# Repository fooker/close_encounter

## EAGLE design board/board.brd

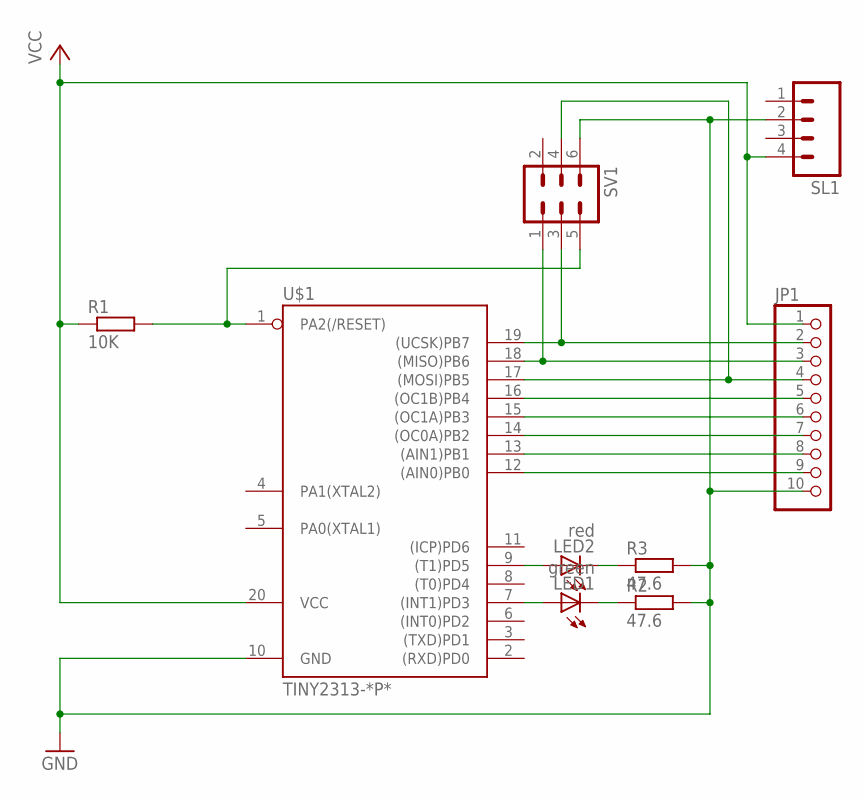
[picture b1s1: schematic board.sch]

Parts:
JP1: PINHD-1X10; 1X10
LED1: green; LED3MM
LED2: red; LED3MM
R1: 10K; 0207/2V
R2, R3: 47.6; 0207/2V
SL1: M04; 04P
SV1: ML6
U$1: TINY2313-*P*; DIL20

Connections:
GND: JP1.10, R2.2, R3.2, SL1.2, SV1.6, U$1.10 (GND)
unnamed: R1.2, SV1.5, U$1.1 (PA2(/RESET))
unnamed: LED2.A, U$1.9 ((T1)PD5)
unnamed: LED1.K (C), R2.1
unnamed: LED1.A, U$1.7 ((INT1)PD3)
unnamed: LED2.K (C), R3.1
unnamed: JP1.3, SV1.1, U$1.18 ((MISO)PB6)
unnamed: JP1.2, SV1.3, U$1.19 ((UCSK)PB7)
unnamed: JP1.4, SV1.4, U$1.17 ((MOSI)PB5)
unnamed: JP1.5, U$1.16 ((OC1B)PB4)
unnamed: JP1.6, U$1.15 ((OC1A)PB3)
unnamed: JP1.7, U$1.14 ((OC0A)PB2)
unnamed: JP1.8, U$1.13 ((AIN1)PB1)
unnamed: JP1.9, U$1.12 ((AIN0)PB0)
VCC: JP1.1, R1.1, SL1.4, U$1.20 (VCC)

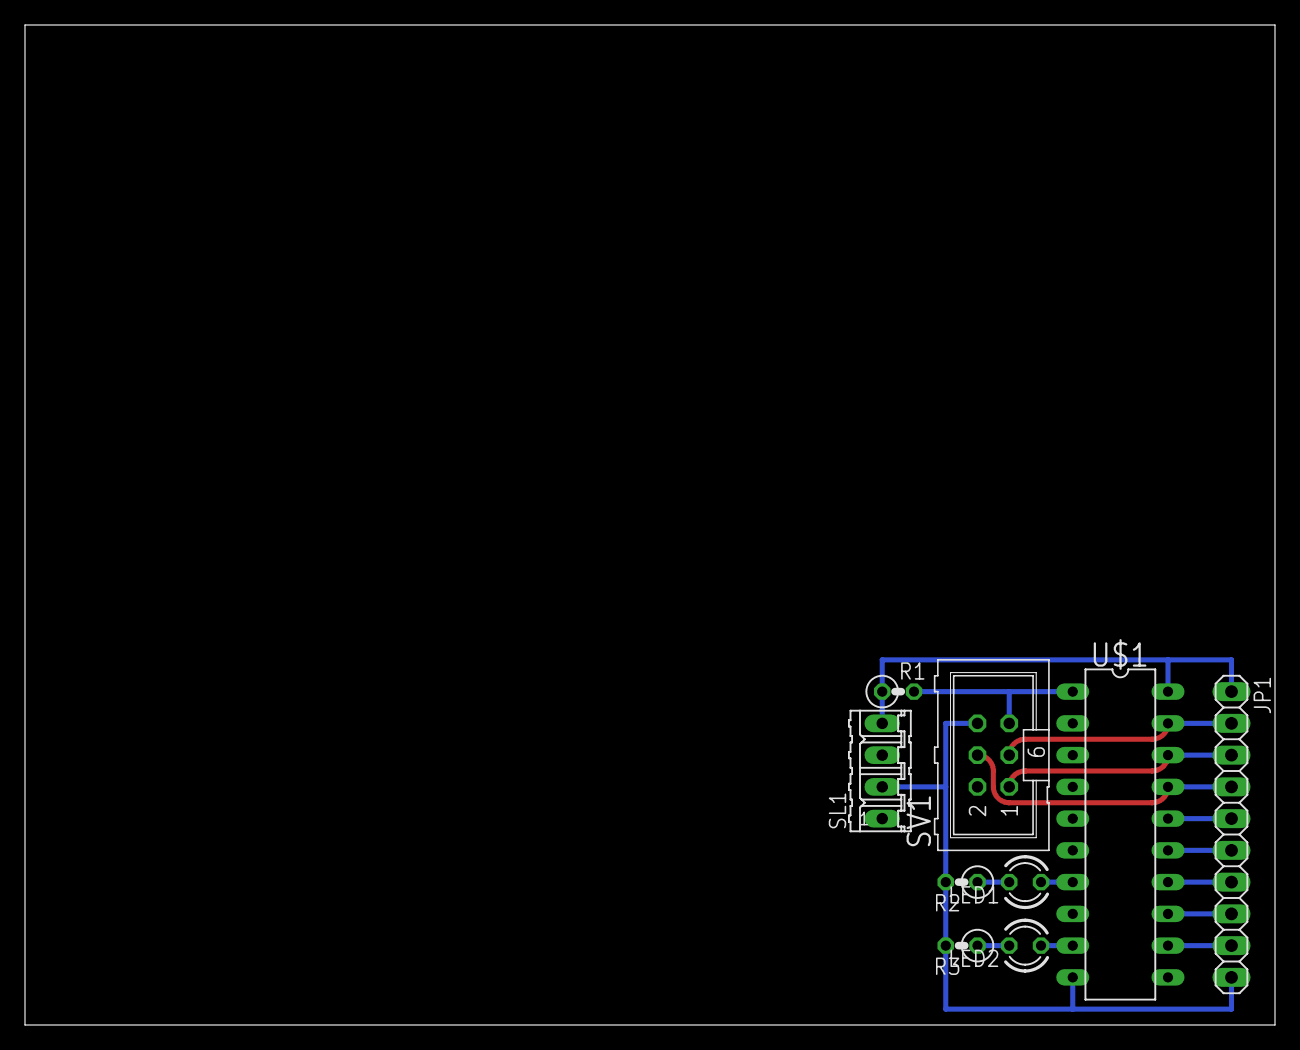
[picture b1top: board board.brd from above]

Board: 2 copper layers, 100.0 x 80.0 mm, 9 parts (0 on the bottom side), 15 nets.

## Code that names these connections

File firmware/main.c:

#include <stdlib.h>
#include <util/delay.h>
#include <avr/io.h>


int main() {
  // Configure output pins
  DDRB = (1 << PB1)
       | (1 << PB2)
       | (1 << PB3)
       | (1 << PB4)
       | (1 << PB5)
       ;
  DDRD = (1 << PD3)
       | (1 << PD5)
       ;

  // Ensure all channels are off
  PORTB = ~( (0 << PB1)
           | (0 << PB2)
           | (0 << PB3)
           | (0 << PB4)
           | (0 << PB5))
           ;

  // Turn on red LED
  PORTD |= (1 << PD3);

loop:
  // Loop over the rounds
  for (uint8_t i = 0; i < 6; i++) {

    // Select two distinct random numbers
    uint8_t b1 = rand() % 5;
    uint8_t b2 = rand() % 4;
    if (b2 == b1) b2 = 4;

    // Build channel masks from random numbers
    uint8_t m1 = (uint8_t[]) { (1 << PB1),
                               (1 << PB2),
                               (1 << PB3),
                               (1 << PB4),
                               (1 << PB5) }[b1];
    uint8_t m2 = (uint8_t[]) { (1 << PB1),
                               (1 << PB2),
                               (1 << PB3),
                               (1 << PB4),
                               (1 << PB5) }[b2];

    // Turn on green LED
    PORTD |= (1 << PD5);

    // Turn on selected channels
    PORTB = ~(m1 | m2);

    // Let lights heat up
    _delay_ms(600);

    // Turn off channels
    PORTB = ~( (0 << PB1)
             | (0 << PB2)
             | (0 << PB3)
             | (0 << PB4)
             | (0 << PB5) )
             ;

    // Turn off green LED
    PORTD &= ~(1 << PD5);

    // Let lights cool down
    _delay_ms(300);
  }

  // Turn on green LED
  PORTD |= (1 << PD5);

  // Delay a random time until next set of rounds (30..60] seconds
  uint8_t s = 30 + (rand() % 30);
  for (uint8_t i = 0; i < s; i++) {
    _delay_ms(1000);

    // Toggle green LED
    PORTD ^= (1 << PD5);
  }

  // Turn off green LED
  PORTD &= ~(1 << PD5);

  goto loop;
}

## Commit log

2014-03-16 Schematics added and firmware changed to reflect final schematics
